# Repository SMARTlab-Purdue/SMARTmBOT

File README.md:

# SMART lab multi-roBOT (SMARTmBOT)

## Objectives
The goal of this repository is to introduce a new, customizable, scalable, and fully opensource mobile robot platform, called SMARTmBOT (v2022). In this repository, we provide a detailed tutorial, and all design files and source codes so that you can build your own SMARTmBOT with off-the-shelf components and also customize its design and functionalities according to your needs. SMARTmBOT supports a new Robot Operating System 2 (ROS2) on Raspberry Pi 4, and we expect SMARTmBOT to be definitely useful for studying the basics of robotics, especially mobile robotics. SMARTmBOT can also be used to study advanced topics such as swarm robotics.

## Wiki, Tutorial, and Demonstrations
Please refer to our [Wiki page](https://github.com/SMARTlab-Purdue/SMARTmBOT/wiki) for a detailed tutorial on SMARTmBOT. The content of the tutorial is as follows:

1. [Basic ROS2 Example](https://github.com/SMARTlab-Purdue/SMARTmBOT/wiki/1.-Basic-ROS2-Example)

2. [Build SMARTmBOT (Hardware)](https://github.com/SMARTlab-Purdue/SMARTmBOT/wiki/2.-Build-SMARTmBOT-(Hardware))

3. [Build SMARTmBOT (Software)](https://github.com/SMARTlab-Purdue/SMARTmBOT/wiki/3.-Build-SMARTmBOT-(Software))

4. [SMARTmBOT Examples](https://github.com/SMARTlab-Purdue/SMARTmBOT/wiki/4.-SMARTmBOT-Examples)

You can also read or download a PDF version of [SMARTmBOT Guide/Manual](https://github.com/SMARTlab-Purdue/SMARTmBOT/blob/main/Documents/SMARTmBOT_Manual.pdf), and watch a full demo video of the SMARTmBOT at <https://youtu.be/uniaTWcCeDM>.

## Contact
If you have any questions or find any issues on SMARTmBOT, please feel free to contact us. We will fix and update them as soon as possible.

## Contributors
All of the contributors are with [SMART Lab](http://www.smart-laboratory.org/index.html), Department of Computer and Information Technology, Purdue University, West Lafayette, IN 47907, USA.<br />

<table>
  <tr>

<td align="center"><a href="http://www.smart-laboratory.org/group/Jaeeun_Kim.html"><br />
              <sub><b><a href="http://www.smart-laboratory.org/group/Jaeeun_Kim.html" title="personal_website">🌍Jaeeun Kim</b></sub></a><br />
<sub><b>Software</b></sub></a><br />
<sub><b><a href="mailto: kim2592@purdue.edu" title="contact">kim2592@purdue.edu </a></b></sub></a><br />

<td align="center"><a href="http://www.smart-laboratory.org/group/Wonse_Jo.html"><br />
          <sub><b><a href="http://www.smart-laboratory.org/group/Wonse_Jo.html" title="personal_website">🌍Wonse Jo</b></sub></a><br />
<sub><b>Hardware</b></sub></a><br />
<sub><b><a href="mailto: jow@purdue.edu" title="contact">jow@purdue.edu</a></b></sub></a><br />
</td>
<td align="center"><a href="http://www.smart-laboratory.org/group/bcm.html"><br />
  <sub><b><a href="http://www.smart-laboratory.org/group/bcm.html" title="personal_website">🌍Byung-Cheol Min</b></sub></a><br />
<sub><b>Director</b></sub></a><br />
<sub><b><a href="mailto: minb@purdue.edu" title="contact">minb@purdue.edu</a></b></sub></a><br />

  </tr>

</table>

## Acknowledgement

This material is based upon work supported by the National Science Foundation under [Grant No. IIS-1846221](https://www.nsf.gov/awardsearch/showAward?AWD_ID=1846221&HistoricalAwards=false&_ga=2.259294090.1882798323.1621529444-1742909408.1612301322). Any opinions, findings, and conclusions or recommendations expressed in this material are those of the author(s) and do not necessarily reflect the views of the National Science Foundation.

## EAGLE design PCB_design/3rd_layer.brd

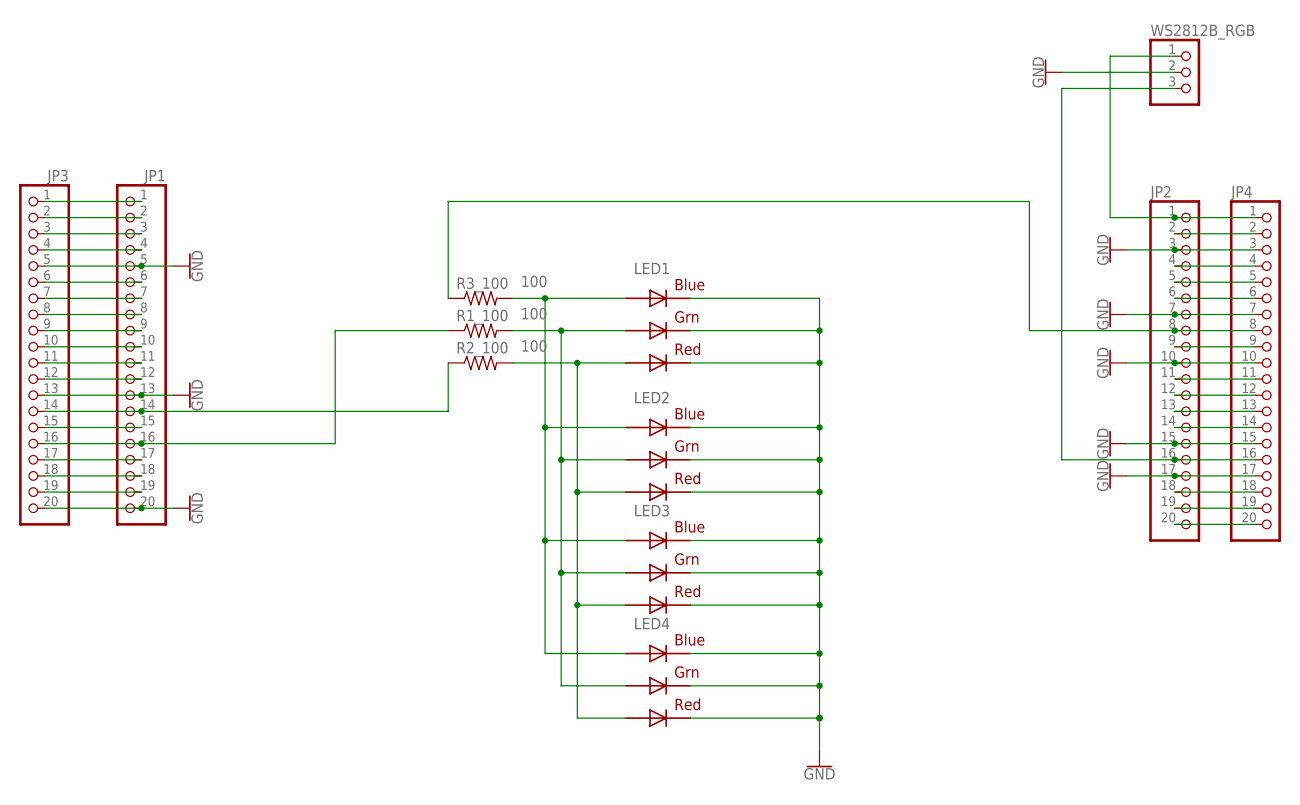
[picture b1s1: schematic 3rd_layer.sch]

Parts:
JP1, JP2, JP3, JP4: PINHD-1X20; 1X20
LED1, LED2, LED3, LED4: RGBLED5050
R1_100, R2_100, R3_100: 100; R0603
WS2812B_RGB: PINHD-1X3/90; 1X03/90

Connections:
GND: JP1.5, JP1.13, JP1.20, JP2.3, JP2.7, JP2.10, JP2.15, JP2.17, JP3.5, JP3.13, JP3.20, JP4.3, JP4.7, JP4.10, JP4.15, JP4.17, LED1.4 (BLUE_C), LED1.5 (RED_C), LED1.6 (GREEN_C), LED2.4 (BLUE_C), LED2.5 (RED_C), LED2.6 (GREEN_C), LED3.4 (BLUE_C), LED3.5 (RED_C), LED3.6 (GREEN_C), LED4.4 (BLUE_C), LED4.5 (RED_C), LED4.6 (GREEN_C), WS2812B_RGB.2
unnamed: JP2.8, JP4.8, R3_100.1
unnamed: JP1.10, JP3.10
unnamed: JP1.14, JP3.14, R2_100.1
unnamed: JP1.9, JP3.9
unnamed: JP1.3, JP3.3
unnamed: JP1.1, JP3.1
unnamed: JP1.2, JP3.2
unnamed: JP1.4, JP3.4
unnamed: JP1.6, JP3.6
unnamed: JP1.7, JP3.7
unnamed: JP1.8, JP3.8
unnamed: JP1.12, JP3.12
unnamed: JP1.15, JP3.15
unnamed: JP1.16, JP3.16, R1_100.1
unnamed: JP1.18, JP3.18
unnamed: JP1.19, JP3.19
unnamed: JP2.1, JP4.1, WS2812B_RGB.1
unnamed: JP2.2, JP4.2
unnamed: JP2.4, JP4.4
unnamed: JP2.5, JP4.5
unnamed: JP2.6, JP4.6
unnamed: JP2.9, JP4.9
unnamed: JP2.12, JP4.12
unnamed: JP2.13, JP4.13
unnamed: JP2.14, JP4.14
unnamed: JP2.16, JP4.16, WS2812B_RGB.3
unnamed: LED1.3 (BLUE_A), LED2.3 (BLUE_A), LED3.3 (BLUE_A), LED4.3 (BLUE_A), R3_100.2
unnamed: LED1.1 (GREEN_A), LED2.1 (GREEN_A), LED3.1 (GREEN_A), LED4.1 (GREEN_A), R1_100.2
unnamed: LED1.2 (RED_A), LED2.2 (RED_A), LED3.2 (RED_A), LED4.2 (RED_A), R2_100.2
unnamed: JP2.18, JP4.18
unnamed: JP2.19, JP4.19
unnamed: JP2.20, JP4.20
unnamed: JP1.17, JP3.17
unnamed: JP1.11, JP3.11
unnamed: JP2.11, JP4.11

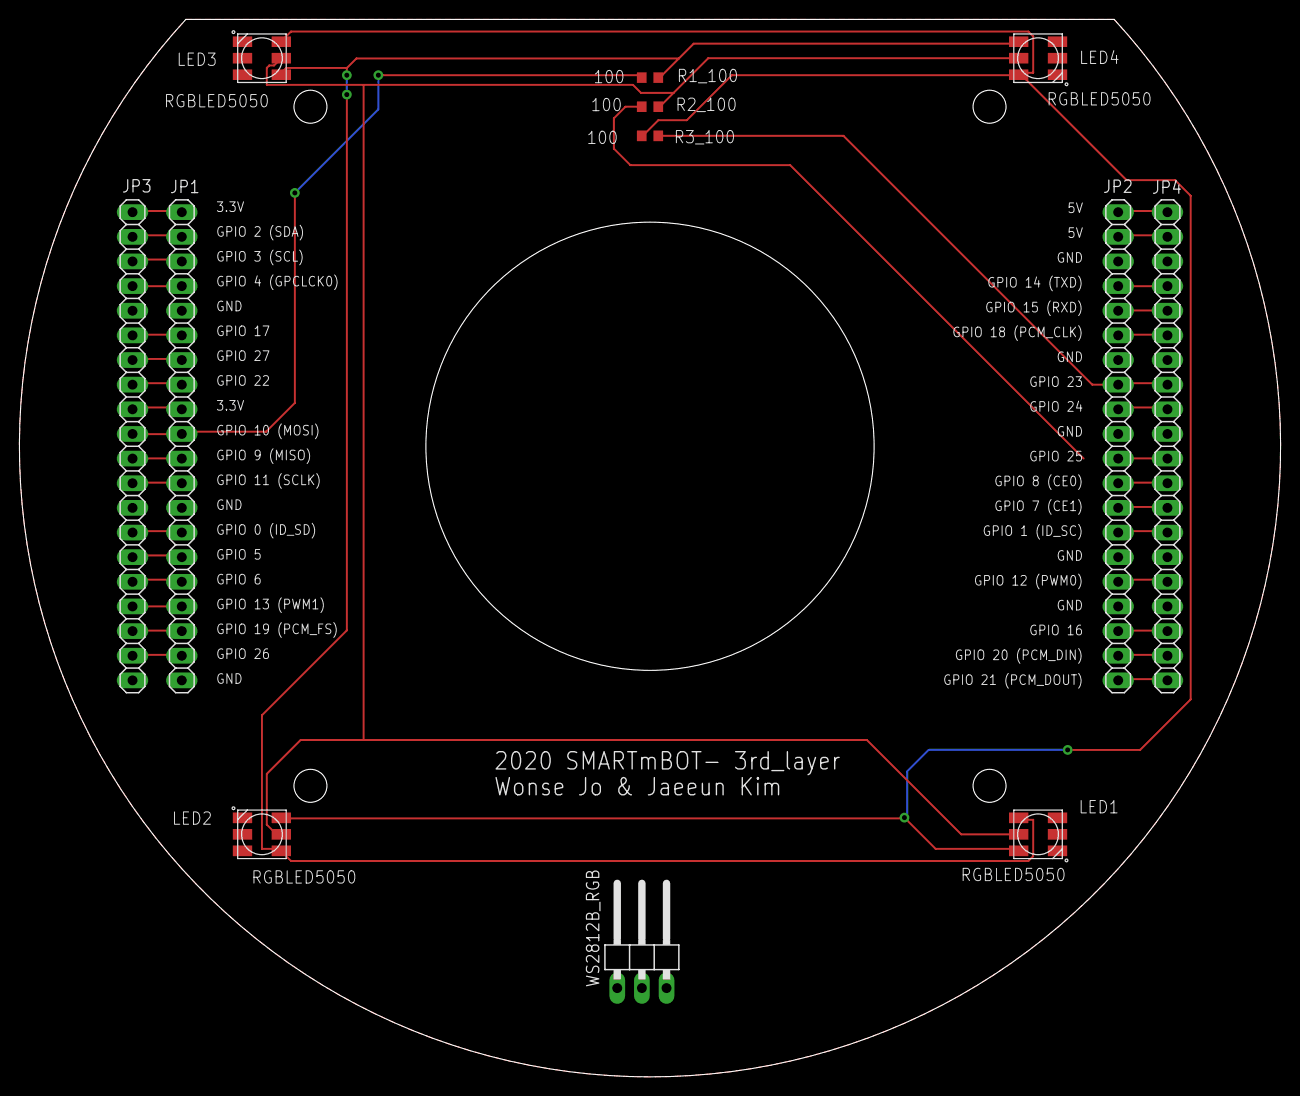
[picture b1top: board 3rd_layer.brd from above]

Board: 2 copper layers, 130.0 x 109.0 mm, 12 parts (0 on the bottom side), 36 nets.

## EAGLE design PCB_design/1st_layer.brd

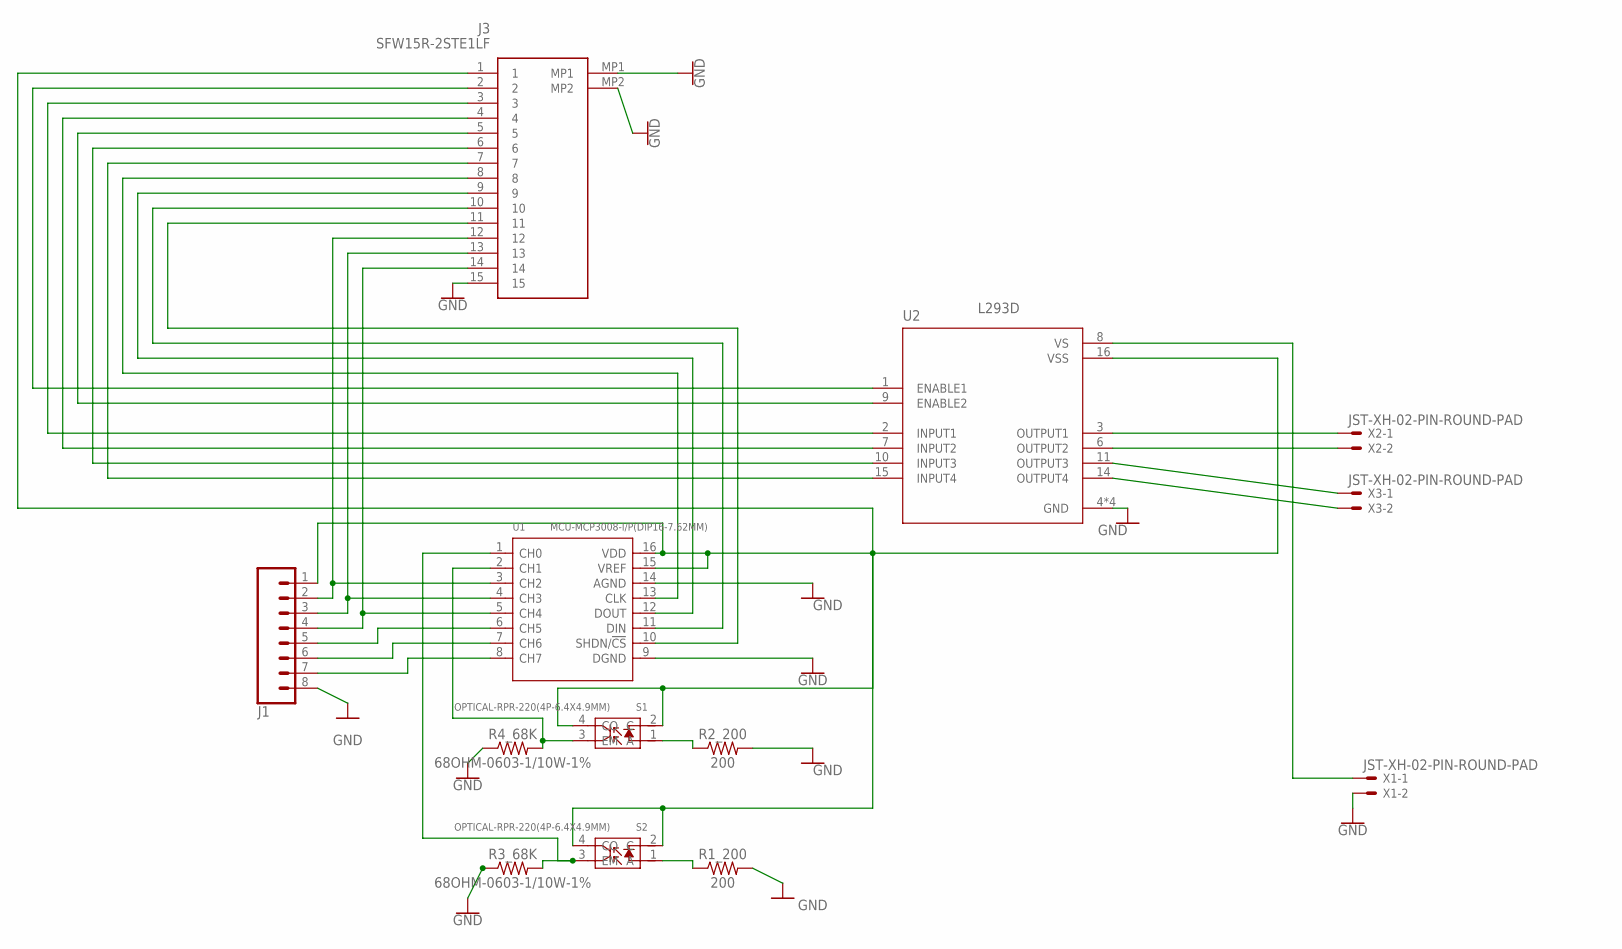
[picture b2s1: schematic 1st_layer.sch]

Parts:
J1: CONN_08LONGPADS; 1X08_LONGPADS
J3: SFW15R-2STE1LF; SFW15R2STE1LF
R1_200, R2_200: 200; 0603
R3_68K, R4_68K: 68OHM-0603-1/10W-1%; 0603
S1, S2: OPTICAL-RPR-220(4P-6.4X4.9MM); SNR4-8.7X4.5X5.8MM
U1: MCU-MCP3008-I/P(DIP16-7.62MM); DIP16-2.54-19.2X7.62MM
U2: L293D; DIP880W50P254L2000H510Q16
X1, X2, X3: JST-XH-02-PIN-ROUND-PAD; JST-XH-02-PACKAGE-ROUND-PAD

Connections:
GND: J1.8, J3.15, J3.MP1, J3.MP2, R1_200.2, R2_200.2, R3_68K.1, R4_68K.1, U1.9 (DGND), U1.14 (AGND), U2.4 (GND), U2.5 (GND), U2.12 (GND), U2.13 (GND), X1.2
unnamed: R2_200.1, S1.1 (A)
unnamed: R1_200.1, S2.1 (A)
unnamed: U2.8 (VS), X1.1
unnamed: R4_68K.2, S1.3 (EM), U1.2 (CH1)
unnamed: R3_68K.2, S2.3 (EM), U1.1 (CH0)
unnamed: U2.3 (OUTPUT1), X2.1
unnamed: U2.6 (OUTPUT2), X2.2
unnamed: U2.11 (OUTPUT3), X3.1
unnamed: U2.14 (OUTPUT4), X3.2
unnamed: J1.2, J3.12, U1.3 (CH2)
unnamed: J3.3, U2.2 (INPUT1)
unnamed: J3.4, U2.7 (INPUT2)
unnamed: J3.5, U2.9 (ENABLE2)
unnamed: J3.2, U2.1 (ENABLE1)
unnamed: J3.6, U2.10 (INPUT3)
unnamed: J3.7, U2.15 (INPUT4)
unnamed: J3.8, U1.13 (CLK)
unnamed: J3.9, U1.12 (DOUT)
unnamed: J3.10, U1.11 (DIN)
unnamed: J3.11, U1.10 (SHDN/!CS)
unnamed: J1.3, J3.13, U1.4 (CH3)
unnamed: J1.4, J3.14, U1.5 (CH4)
unnamed: J1.5, U1.6 (CH5)
unnamed: J1.6, U1.7 (CH6)
unnamed: J1.7, U1.8 (CH7)
VDD: J1.1, J3.1, S1.2 (C), S1.4 (CO), S2.2 (C), S2.4 (CO), U1.15 (VREF), U1.16 (VDD), U2.16 (VSS)

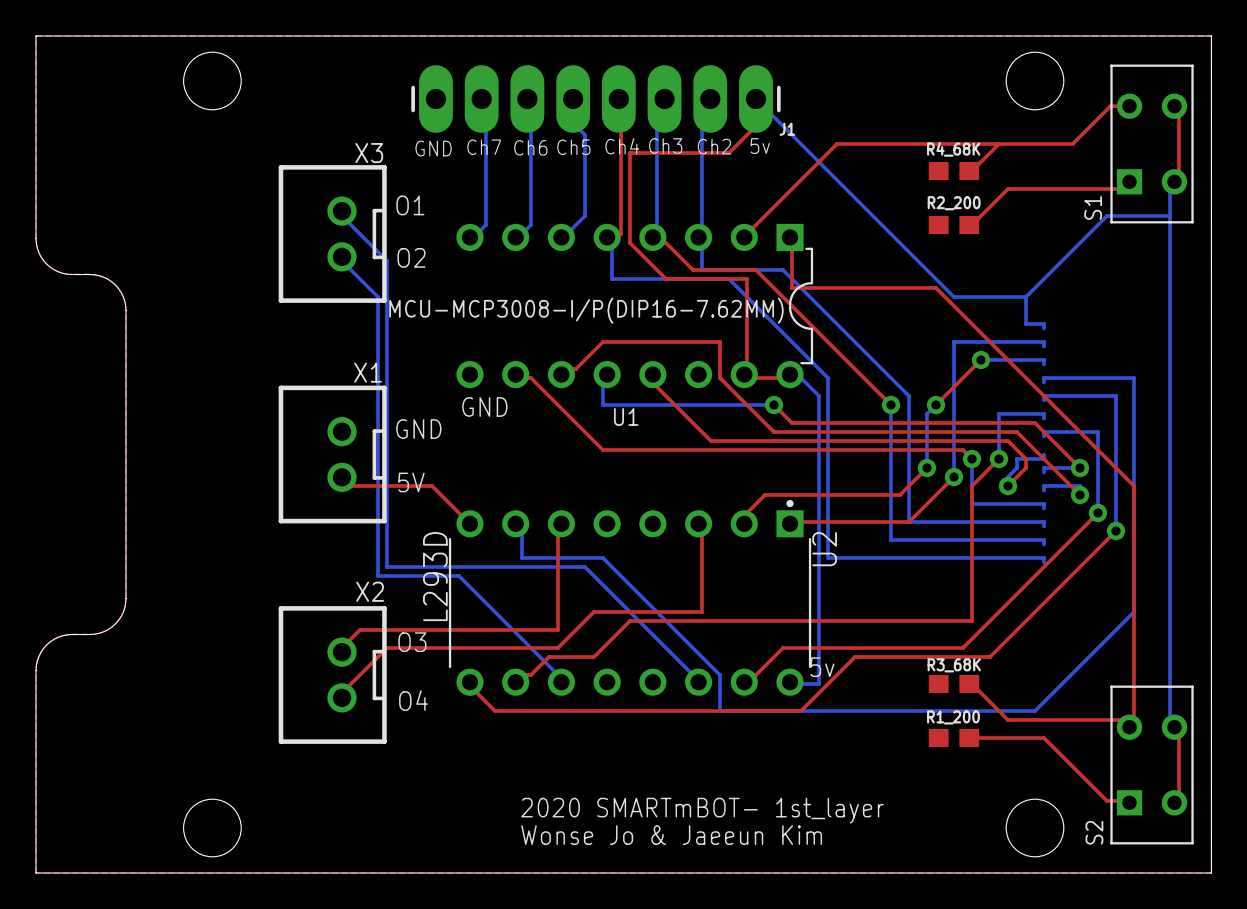
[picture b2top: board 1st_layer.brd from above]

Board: 2 copper layers, 65.3 x 46.5 mm, 13 parts (1 on the bottom side), 27 nets.

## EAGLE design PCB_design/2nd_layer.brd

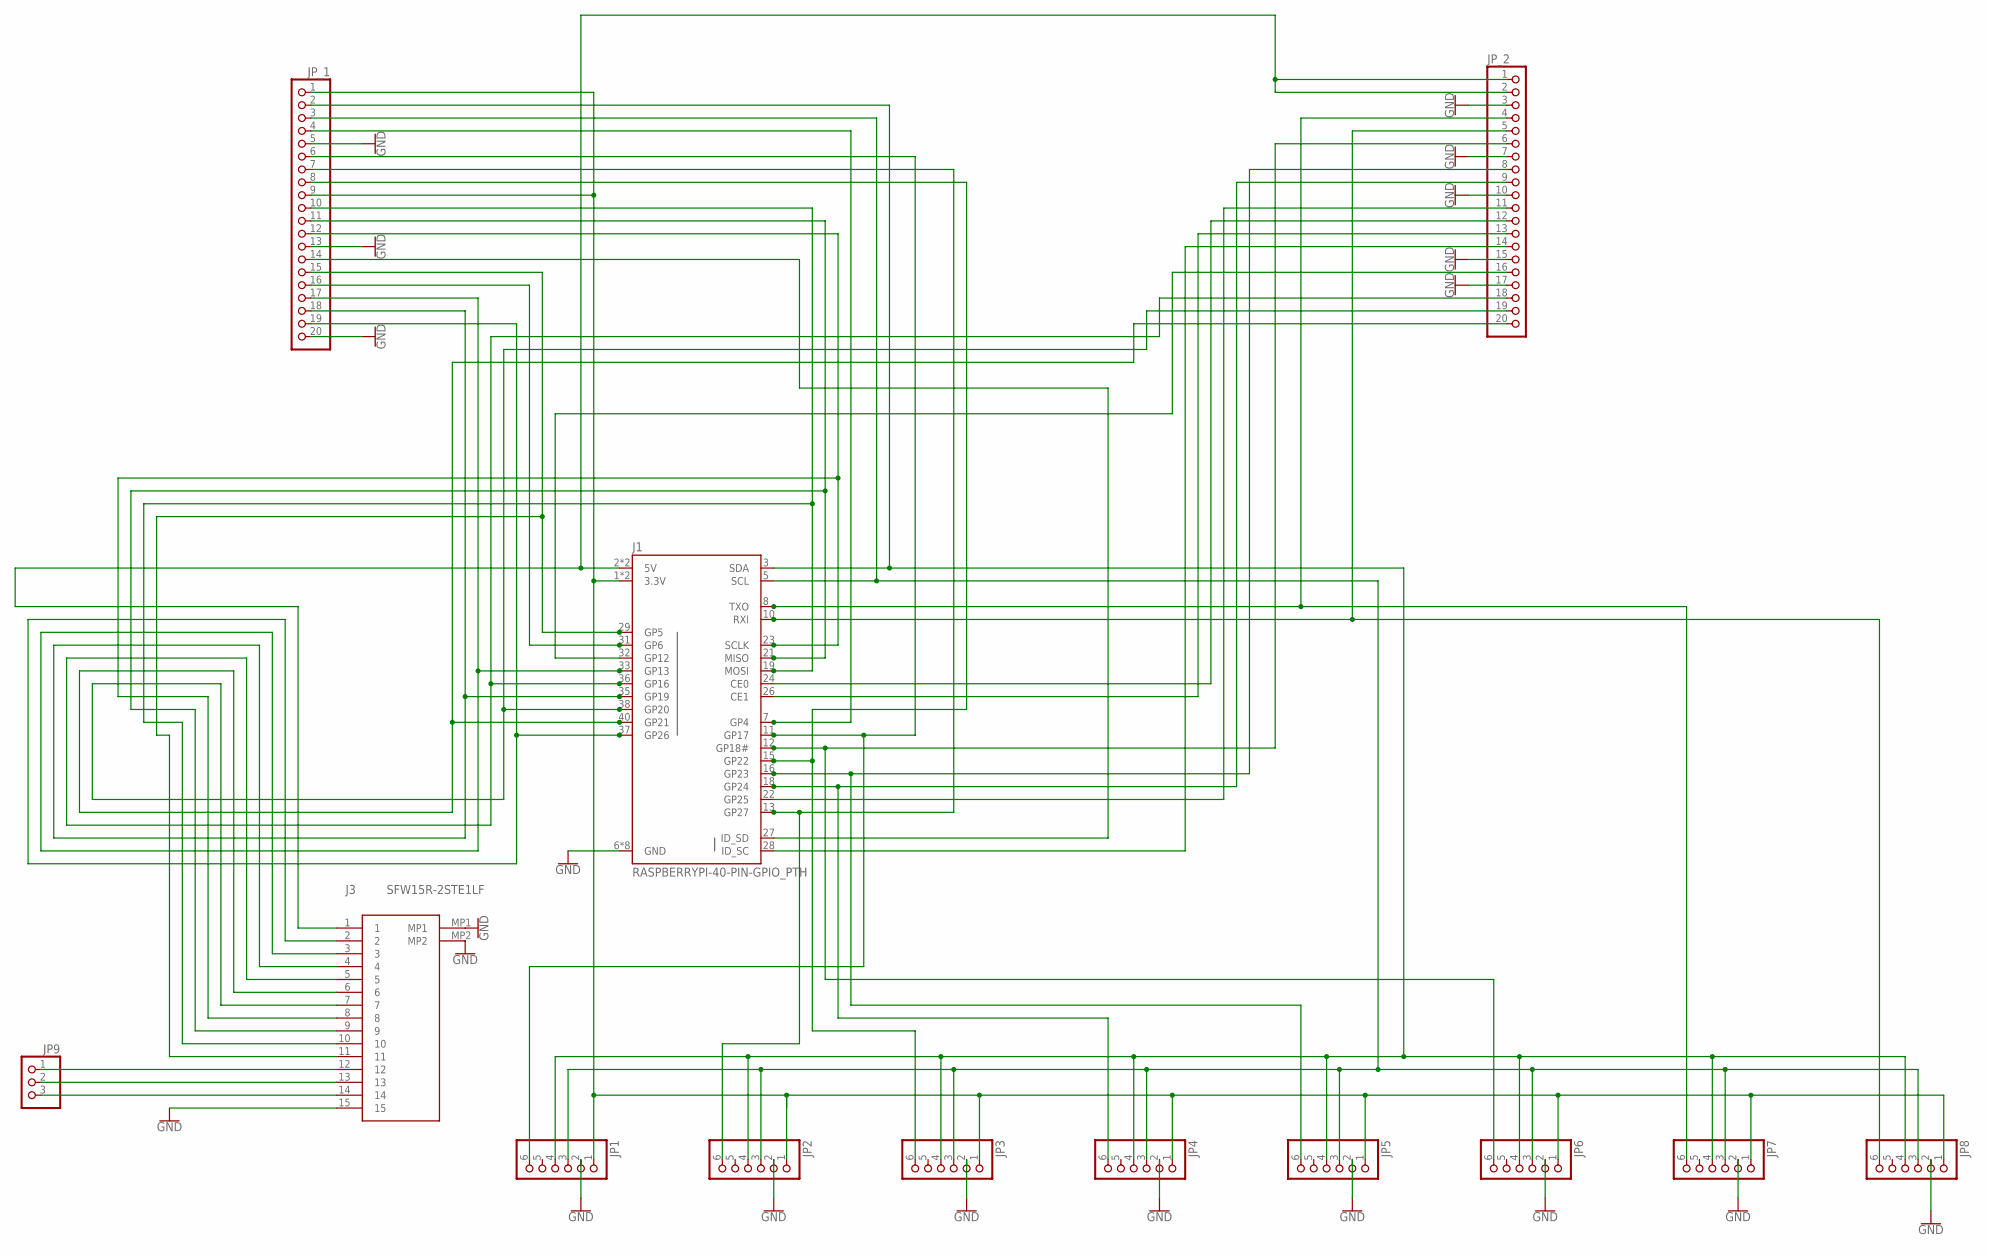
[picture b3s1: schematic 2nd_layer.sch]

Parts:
J1: RASPBERRYPI-40-PIN-GPIO_PTH; 2X20_SHROUDED
J3: SFW15R-2STE1LF; SFW15R2STE1LF
JP1, JP2, JP3, JP4, JP5, JP6, JP7, JP8: PINHD-1X6; 1X06
JP9: PINHD-1X3; 1X03
JP_1, JP_2: PINHD-1X20; 1X20

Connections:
GND: J1.6 (GND), J1.9 (GND), J1.14 (GND), J1.20 (GND), J1.25 (GND), J1.30 (GND), J1.34 (GND), J1.39 (GND), J3.15, J3.MP1, J3.MP2, JP1.2, JP2.2, JP3.2, JP4.2, JP5.2, JP6.2, JP7.2, JP8.2, JP_1.5, JP_1.13, JP_1.20, JP_2.3, JP_2.7, JP_2.10, JP_2.15, JP_2.17
unnamed: J1.7 (GP4), JP_1.4
unnamed: J1.31 (GP6), JP_1.16
unnamed: J1.22 (GP25), JP_2.11
unnamed: J1.2 (5V), J1.4 (5V), J3.1, JP_2.1, JP_2.2
unnamed: J1.1 (3.3V), J1.17 (3.3V), JP1.1, JP2.1, JP3.1, JP4.1, JP5.1, JP6.1, JP7.1, JP8.1, JP_1.1, JP_1.9
unnamed: J1.27 (ID_SD), JP_1.14
unnamed: J1.5 (SCL), JP1.3, JP2.3, JP3.3, JP4.3, JP5.3, JP6.3, JP7.3, JP8.3, JP_1.3
unnamed: J1.3 (SDA), JP1.4, JP2.4, JP3.4, JP4.4, JP5.4, JP6.4, JP7.4, JP8.4, JP_1.2
unnamed: J1.11 (GP17), JP1.6, JP_1.6
unnamed: J1.13 (GP27), JP2.6, JP_1.7
unnamed: J1.15 (GP22), JP3.6, JP_1.8
unnamed: J1.18 (GP24), JP4.6, JP_2.9
unnamed: J1.16 (GP23), JP5.6, JP_2.8
unnamed: J1.12 (GP18#), JP6.6, JP_2.6
unnamed: J1.8 (TXO), JP7.6, JP_2.4
unnamed: J1.10 (RXI), JP8.6, JP_2.5
unnamed: J1.37 (GP26), J3.2, JP_1.19
unnamed: J1.33 (GP13), J3.3, JP_1.17
unnamed: J1.35 (GP19), J3.4, JP_1.18
unnamed: J1.36 (GP16), J3.5, JP_2.18
unnamed: J1.40 (GP21), J3.6, JP_2.20
unnamed: J1.38 (GP20), J3.7, JP_2.19
unnamed: J1.23 (SCLK), J3.8, JP_1.12
unnamed: J1.21 (MISO), J3.9, JP_1.11
unnamed: J1.19 (MOSI), J3.10, JP_1.10
unnamed: J1.29 (GP5), J3.11, JP_1.15
unnamed: J1.24 (CE0), JP_2.12
unnamed: J1.26 (CE1), JP_2.13
unnamed: J1.28 (ID_SC), JP_2.14
unnamed: J1.32 (GP12), JP_2.16
unnamed: J3.12, JP9.1
unnamed: J3.13, JP9.2
unnamed: J3.14, JP9.3

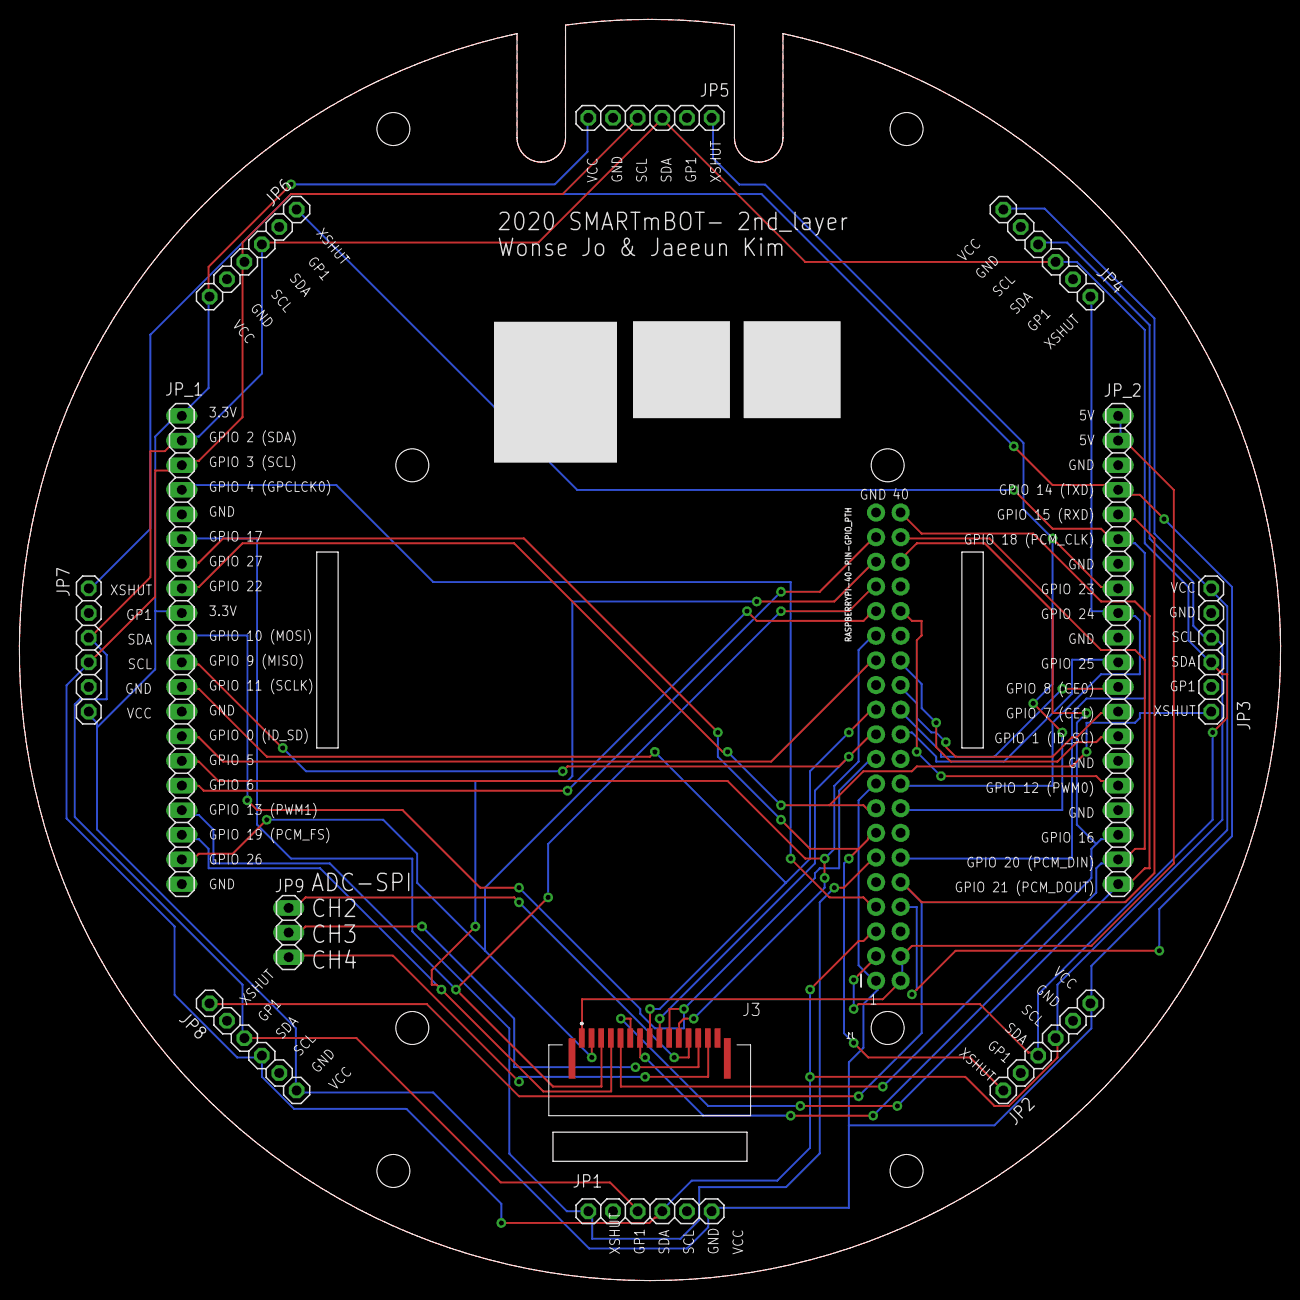
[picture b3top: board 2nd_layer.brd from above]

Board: 2 copper layers, 130.0 x 130.0 mm, 13 parts (1 on the bottom side), 34 nets.

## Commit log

2021-05-23 moved all file from the Purdue git
2021-05-24 updated images
2021-05-24 uploaded images
2021-05-24 moved files to wiki folder.
2021-05-24 uploaded system images
2021-05-26 deleted slddrw files
2022-01-04 upload a revised manual pdf
2022-01-05 updated documents.
2022-02-27 Updated navigation controllers of SMARTmBOT.

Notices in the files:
parts and their libraries:
SparkFun-Resistors: Licensing: Creative Commons ShareAlike 4.0 International - https://creativecommons.org/licenses/by-sa/4.0
